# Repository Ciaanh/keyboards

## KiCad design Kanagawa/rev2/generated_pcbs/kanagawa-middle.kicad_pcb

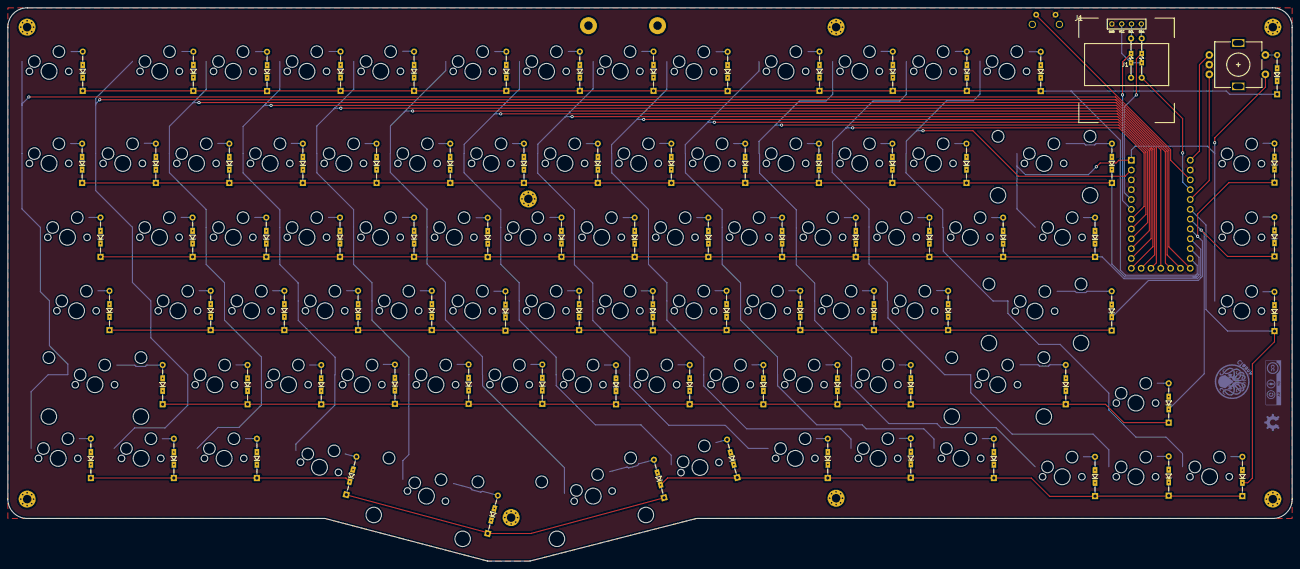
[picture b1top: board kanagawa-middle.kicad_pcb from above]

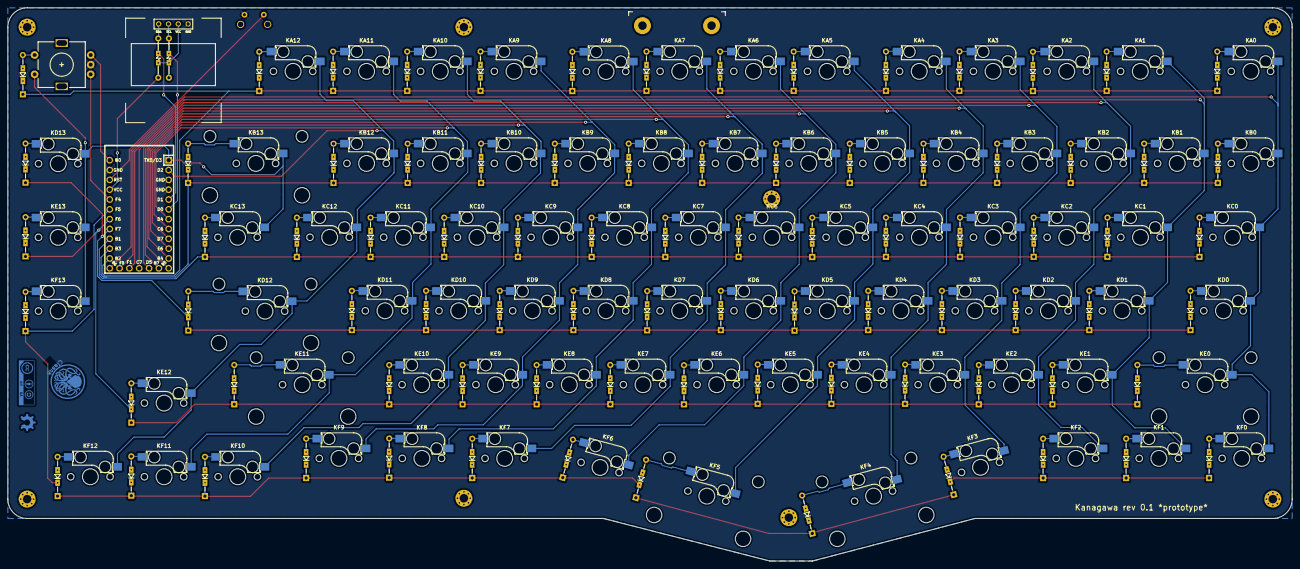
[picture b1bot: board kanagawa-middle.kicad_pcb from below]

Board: 2 copper layers, 332.0 x 143.0 mm, 185 parts (3 on the bottom side), 111 nets.

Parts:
DA0, DA1, DA2, DA3, DA4, DA5, DA6, DA7, DA8, DA9, DA10, DA11, DA12, DA13: D; Diode_SMD_THT
DB0, DB1, DB2, DB3, DB4, DB5, DB6, DB7, DB8, DB9, DB10, DB11, DB12, DB13: D; Diode_SMD_THT
DC0, DC1, DC2, DC3, DC4, DC5, DC6, DC7, DC8, DC9, DC10, DC11, DC12, DC13: D; Diode_SMD_THT
DD0, DD1, DD2, DD3, DD4, DD5, DD6, DD7, DD8, DD9, DD10, DD11, DD12, DD13: D; Diode_SMD_THT
DE0, DE1, DE2, DE3, DE4, DE5, DE6, DE7, DE8, DE9, DE10, DE11, DE12, DE13: D; Diode_SMD_THT
DF0, DF1, DF2, DF3, DF4, DF5, DF6, DF7, DF8, DF9, DF10, DF11, DF12, DF13: D; Diode_SMD_THT
J1: Conn_01x04; OLED_128x64_I2C
KA0, KA1, KA2, KA3, KA4, KA5, KA6, KA7, KA8, KA9, KA10, KA11, KA12: KEY_SW; SW_Cherry_MX_1.00u_Hotswap
KB0, KB1, KB2, KB3, KB4, KB5, KB6, KB7, KB8, KB9, KB10, KB11, KB12: KEY_SW; SW_Cherry_MX_1.00u_Hotswap
KB13: KEY_SW; SW_Cherry_MX_2.00u_Hotswap
KC0, KC13: KEY_SW; SW_Cherry_MX_1.50u_Hotswap
KC1, KC2, KC3, KC4, KC5, KC6, KC7, KC8, KC9, KC10, KC11, KC12: KEY_SW; SW_Cherry_MX_1.00u_Hotswap
KD0: KEY_SW; SW_Cherry_MX_1.75u_Hotswap
KD1, KD2, KD3, KD4, KD5, KD6, KD7, KD8, KD9, KD10, KD11: KEY_SW; SW_Cherry_MX_1.00u_Hotswap
KD12: KEY_SW; SW_Cherry_MX_2.25u_Hotswap
KD13: KEY_SW; SW_Cherry_MX_1.25u_Hotswap
KE0, KE11: KEY_SW; SW_Cherry_MX_2.25u_Hotswap
KE1, KE2, KE3, KE4, KE5, KE6, KE7, KE8, KE9, KE10, KE12: KEY_SW; SW_Cherry_MX_1.00u_Hotswap
KE13: KEY_SW; SW_Cherry_MX_1.25u_Hotswap
KF0, KF2, KF7, KF9, KF13: KEY_SW; SW_Cherry_MX_1.25u_Hotswap
KF1, KF3, KF6, KF8, KF10, KF11, KF12: KEY_SW; SW_Cherry_MX_1.00u_Hotswap
KF4, KF5: KEY_SW; SW_Cherry_MX_2.00u_Hotswap
LogoMiddle0: LOGO; Ciaanh_signature_back
LogoMiddle1: cc_logo; cc
LogoMiddle2: oshw_logo; oshw
MountBaseMiddleTop1, MountBaseMiddleTop2, MountBaseMiddleTop3, MountBaseMiddleTop4, MountBaseMiddleTop5, MountBaseMiddleTop6, MountBaseMiddleTop7, MountBaseMiddleTop8: MountingHole; MountingHole_2.2mm_M2_Pad_Via
MountMiddle0: MountingHole USB breakout; Keebio_USB-C_breakout_shadow
R1, R2: 4.7k; Resistors_SMD_THT
RSW0: SW_RST
SW99: Rotary_Encoder_Switch; RotaryEncoder_Alps_EC11E-Switch_Vertical_H20mm
U0: Elite-C; Elite-C-29pin-holes

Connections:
/SW99B: DA13.2, SW99.S2
ENCA: SW99.A, U0.24
ENCB: SW99.B, U0.20
GND: J1.1, RSW0.2, SW99.C, U0.3, U0.4, U0.23
unnamed: DA0.2, KA0.2
unnamed: DA1.2, KA1.2
unnamed: DA2.2, KA2.2
unnamed: DA3.2, KA3.2
unnamed: DA4.2, KA4.2
unnamed: DA5.2, KA5.2
unnamed: DA6.2, KA6.2
unnamed: DA7.2, KA7.2
unnamed: DA8.2, KA8.2
unnamed: DA9.2, KA9.2
unnamed: DA10.2, KA10.2
unnamed: DA11.2, KA11.2
unnamed: DA12.2, KA12.2
unnamed: DB0.2, KB0.2
unnamed: DB1.2, KB1.2
unnamed: DB2.2, KB2.2
unnamed: DB3.2, KB3.2
unnamed: DB4.2, KB4.2
unnamed: DB5.2, KB5.2
unnamed: DB6.2, KB6.2
unnamed: DB7.2, KB7.2
unnamed: DB8.2, KB8.2
unnamed: DB9.2, KB9.2
unnamed: DB10.2, KB10.2
unnamed: DB11.2, KB11.2
unnamed: DB12.2, KB12.2
unnamed: DB13.2, KB13.2
unnamed: DC0.2, KC0.2
unnamed: DC1.2, KC1.2
unnamed: DC2.2, KC2.2
unnamed: DC3.2, KC3.2
unnamed: DC4.2, KC4.2
unnamed: DC5.2, KC5.2
unnamed: DC6.2, KC6.2
unnamed: DC7.2, KC7.2
unnamed: DC8.2, KC8.2
unnamed: DC9.2, KC9.2
unnamed: DC10.2, KC10.2
unnamed: DC11.2, KC11.2
unnamed: DC12.2, KC12.2
unnamed: DC13.2, KC13.2
unnamed: DD0.2, KD0.2
unnamed: DD1.2, KD1.2
unnamed: DD2.2, KD2.2
unnamed: DD3.2, KD3.2
unnamed: DD4.2, KD4.2
unnamed: DD5.2, KD5.2
unnamed: DD6.2, KD6.2
unnamed: DD7.2, KD7.2
unnamed: DD8.2, KD8.2
unnamed: DD9.2, KD9.2
unnamed: DD10.2, KD10.2
unnamed: DD11.2, KD11.2
unnamed: DD12.2, KD12.2
unnamed: DD13.2, KD13.2
unnamed: DE0.2, KE0.2
unnamed: DE1.2, KE1.2
unnamed: DE2.2, KE2.2
unnamed: DE3.2, KE3.2
unnamed: DE4.2, KE4.2
unnamed: DE5.2, KE5.2
unnamed: DE6.2, KE6.2
unnamed: DE7.2, KE7.2
unnamed: DE8.2, KE8.2
unnamed: DE9.2, KE9.2
unnamed: DE10.2, KE10.2
unnamed: DE11.2, KE11.2
unnamed: DE12.2, KE12.2
unnamed: DE13.2, KE13.2
unnamed: DF0.2, KF0.2
unnamed: DF1.2, KF1.2
unnamed: DF2.2, KF2.2
unnamed: DF3.2, KF3.2
unnamed: DF4.2, KF4.2
unnamed: DF5.2, KF5.2
unnamed: DF6.2, KF6.2
unnamed: DF7.2, KF7.2
unnamed: DF8.2, KF8.2
unnamed: DF9.2, KF9.2
unnamed: DF10.2, KF10.2
unnamed: DF11.2, KF11.2
unnamed: DF12.2, KF12.2
unnamed: DF13.2, KF13.2
RESET: RSW0.1, U0.22
SCL: J1.3, R2.1, U0.6
SDA: J1.4, R1.1, U0.5
VCC: J1.2, R1.2, R2.2, U0.21
col00: KA0.1, KB0.1, KC0.1, KD0.1, KE0.1, KF0.1, U0.13
col01: KA1.1, KB1.1, KC1.1, KD1.1, KE1.1, KF1.1, U0.29
col02: KA2.1, KB2.1, KC2.1, KD2.1, KE2.1, KF2.1, U0.28
col03: KA3.1, KB3.1, KC3.1, KD3.1, KE3.1, KF3.1, U0.27
col04: KA4.1, KB4.1, KC4.1, KD4.1, KE4.1, KF4.1, U0.26
col05: KA5.1, KB5.1, KC5.1, KD5.1, KE5.1, KF5.1, U0.25
col06: KA6.1, KB6.1, KC6.1, KD6.1, KE6.1, KF6.1, U0.12
col07: KA7.1, KB7.1, KC7.1, KD7.1, KE7.1, KF7.1, U0.11
col08: KA8.1, KB8.1, KC8.1, KD8.1, KE8.1, KF8.1, U0.10
col09: KA9.1, KB9.1, KC9.1, KD9.1, KE9.1, KF9.1, U0.9
col10: KA10.1, KB10.1, KC10.1, KD10.1, KE10.1, KF10.1, U0.8
col11: KA11.1, KB11.1, KC11.1, KD11.1, KE11.1, KF11.1, U0.7
col12: KA12.1, KB12.1, KC12.1, KD12.1, KE12.1, KF12.1, U0.2
col13: KB13.1, KC13.1, KD13.1, KE13.1, KF13.1, SW99.S1, U0.1
row00: DA0.1, DA1.1, DA2.1, DA3.1, DA4.1, DA5.1, DA6.1, DA7.1, DA8.1, DA9.1, DA10.1, DA11.1, DA12.1, DA13.1, U0.14
row01: DB0.1, DB1.1, DB2.1, DB3.1, DB4.1, DB5.1, DB6.1, DB7.1, DB8.1, DB9.1, DB10.1, DB11.1, DB12.1, DB13.1, U0.15
row02: DC0.1, DC1.1, DC2.1, DC3.1, DC4.1, DC5.1, DC6.1, DC7.1, DC8.1, DC9.1, DC10.1, DC11.1, DC12.1, DC13.1, U0.16
row03: DD0.1, DD1.1, DD2.1, DD3.1, DD4.1, DD5.1, DD6.1, DD7.1, DD8.1, DD9.1, DD10.1, DD11.1, DD12.1, DD13.1, U0.17
row04: DE0.1, DE1.1, DE2.1, DE3.1, DE4.1, DE5.1, DE6.1, DE7.1, DE8.1, DE9.1, DE10.1, DE11.1, DE12.1, DE13.1, U0.18
row05: DF0.1, DF1.1, DF2.1, DF3.1, DF4.1, DF5.1, DF6.1, DF7.1, DF8.1, DF9.1, DF10.1, DF11.1, DF12.1, DF13.1, U0.19
